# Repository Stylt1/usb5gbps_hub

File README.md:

View this project on [CADLAB.io](https://cadlab.io/project/30484). 

# usb5gbps_hub
USB-C hub that works on USB 3.2 Gen 1 protocol

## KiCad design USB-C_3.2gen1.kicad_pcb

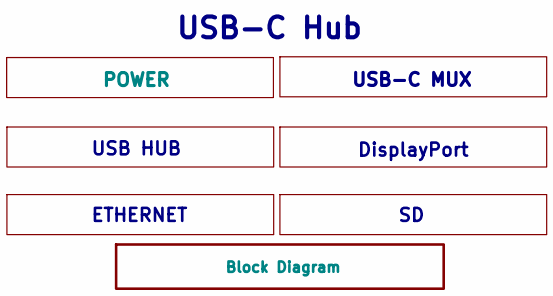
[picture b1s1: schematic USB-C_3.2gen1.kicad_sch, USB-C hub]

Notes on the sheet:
DisplayPort
USB-C MUX
USB HUB
ETHERNET
USB-C Hub

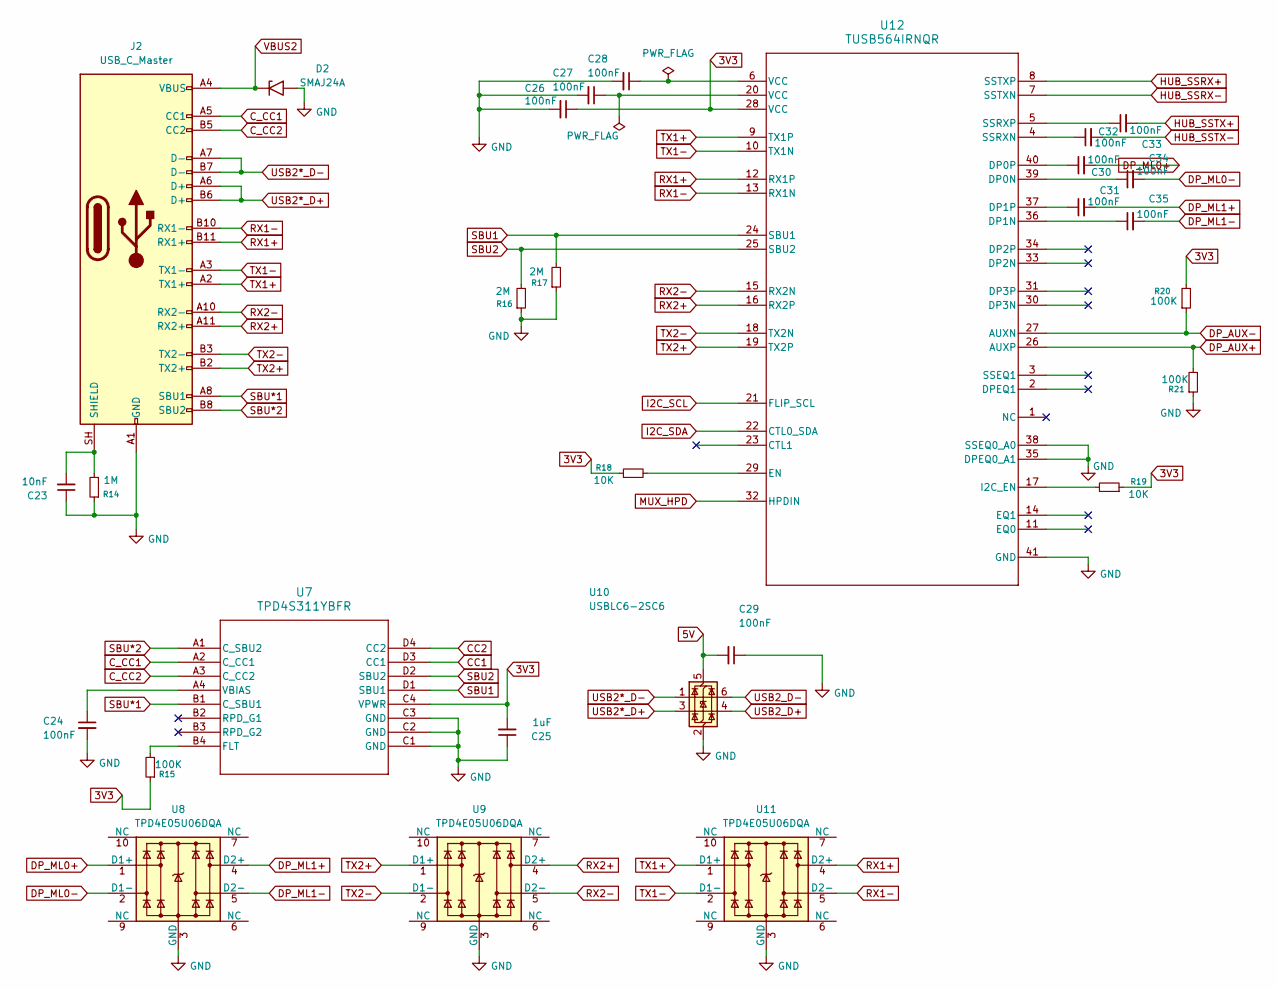
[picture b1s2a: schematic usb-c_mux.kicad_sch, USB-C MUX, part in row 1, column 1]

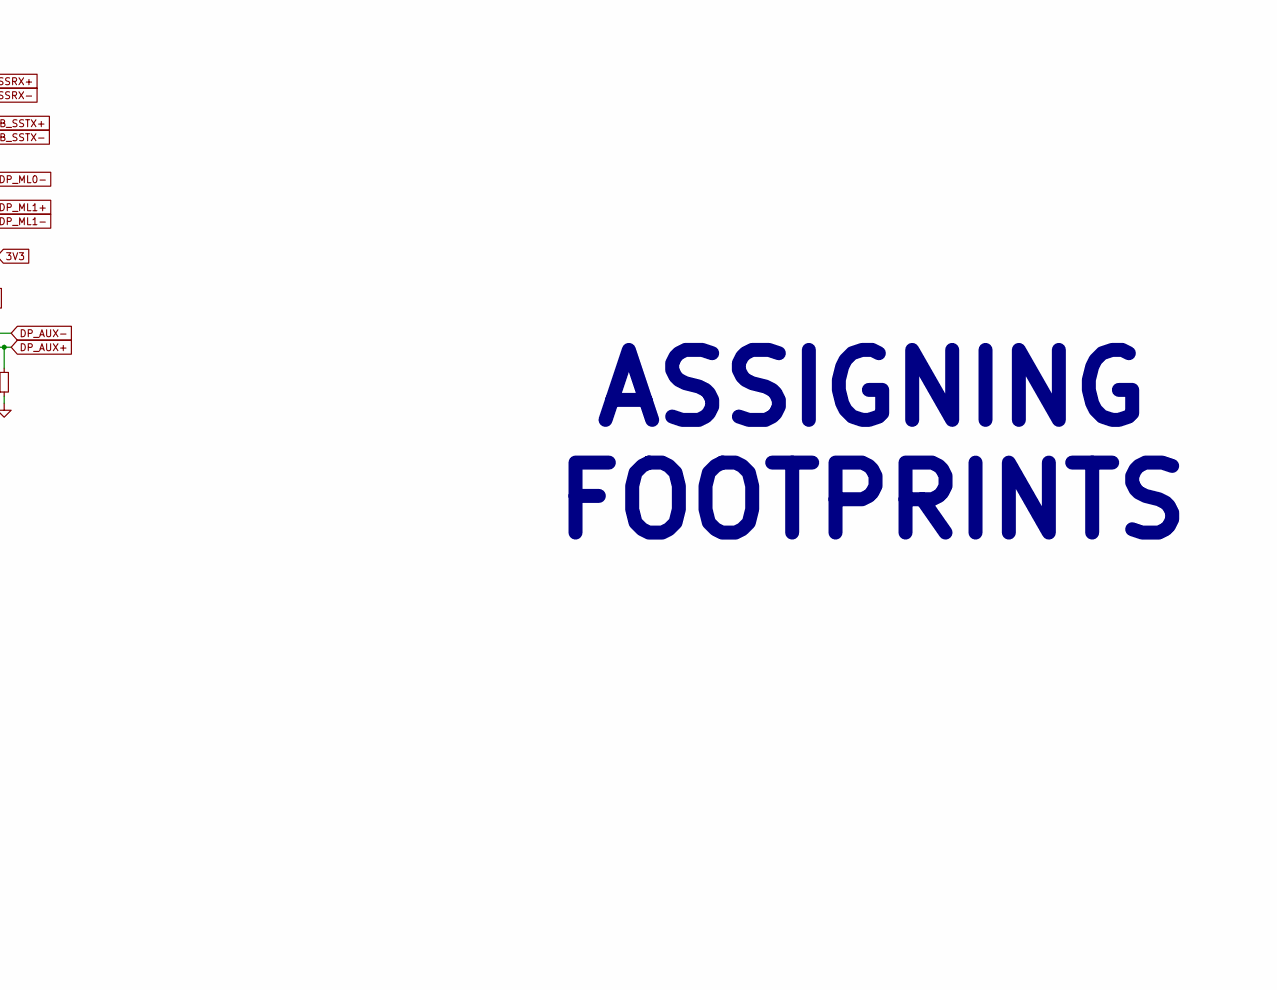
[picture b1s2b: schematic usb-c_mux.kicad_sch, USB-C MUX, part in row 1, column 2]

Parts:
C23: 10nF; C_0603_1608Metric
C24, C26, C27, C28, C29, C30, C31, C32, C33, C34, C35: 100nF; C_0603_1608Metric
C25: 1uF; C_0603_1608Metric
D2: SMAJ24A; D_SMA
J2: USB_C_Master; USB_C_Receptacle_Molex_105450-0101
R14: 1M; R_0603_1608Metric
R15, R20, R21: 100K; R_0603_1608Metric
R16, R17: 2M; R_0603_1608Metric
R18, R19: 10K; R_0603_1608Metric
U7: TPD4S311YBFR; Texas_DSBGA-16_2.39x2.39mm_Layout4x4_P0.5mm
U8, U9, U11: TPD4E05U06DQA; USON-10_2.5x1.0mm_P0.5mm
U10: USBLC6-2SC6; SOT-23-6
U12: TUSB564IRNQR; Texas_RNQ0040A_WQFN-40-1EP_6x4mm_P0.4mm_EP4.7x2.7mm_Thermal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

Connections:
3V3: C25.2, C26.1, R15.1, R18.1, R19.1, R20.2, U7.C4 (VPWR), U12.28 (VCC); also elsewhere on the board
5V: C29.2, U10.5 (VBUS); also elsewhere on the board
CC1: U7.D3 (CC1)
CC2: U7.D4 (CC2)
C_CC1: J2.A5 (CC1), U7.A2 (C_CC1)
C_CC2: J2.B5 (CC2), U7.A3 (C_CC2)
DP_AUX+: R21.2, U12.26 (AUXP); also elsewhere on the board
DP_AUX-: R20.1, U12.27 (AUXN); also elsewhere on the board
DP_ML0+: C30.2, U8.1 (D1+); also elsewhere on the board
DP_ML0-: C34.2, U8.2 (D1-); also elsewhere on the board
DP_ML1+: C31.2, U8.4 (D2+); also elsewhere on the board
DP_ML1-: C35.2, U8.5 (D2-); also elsewhere on the board
GND: C23.1, C24.2, C25.1, C26.2, C27.2, C28.2, C29.1, D2.2 (A2), J2.A1 (GND), J2.A12 (GND), J2.B1 (GND), J2.B12 (GND), R14.1, R16.1, R17.1, R21.1, U7.C1 (GND), U7.C2 (GND), U7.C3 (GND), U8.3 (GND), U8.8 (GND), U9.3 (GND), U9.8 (GND), U10.2 (GND), U11.3 (GND), U11.8 (GND), U12.35 (DPEQ0_A1), U12.38 (SSEQ0_A0), U12.41 (GND); also elsewhere on the board
HUB_SSRX+: U12.8 (SSTXP); also elsewhere on the board
HUB_SSRX-: U12.7 (SSTXN); also elsewhere on the board
HUB_SSTX+: C33.2; also elsewhere on the board
HUB_SSTX-: C32.2; also elsewhere on the board
I2C_SCL: U12.21 (FLIP_SCL); also elsewhere on the board
I2C_SDA: U12.22 (CTL0_SDA); also elsewhere on the board
MUX_HPD: U12.32 (HPDIN); also elsewhere on the board
unnamed: C27.1, U12.20 (VCC)
unnamed: C28.1, U12.6 (VCC)
unnamed: C23.2, J2.SH (SHIELD), R14.2
unnamed: R15.2, U7.B4 (FLT)
unnamed: C24.1, U7.A4 (VBIAS)
unnamed: C34.1, U12.39 (DP0N)
unnamed: C30.1, U12.40 (DP0P)
unnamed: C35.1, U12.36 (DP1N)
unnamed: C31.1, U12.37 (DP1P)
unnamed: R18.2, U12.29 (EN)
unnamed: R19.2, U12.17 (I2C_EN)
unnamed: C32.1, U12.4 (SSRXN)
unnamed: C33.1, U12.5 (SSRXP)
RX1+: J2.B11 (RX1+), U11.4 (D2+), U12.12 (RX1P)
RX1-: J2.B10 (RX1-), U11.5 (D2-), U12.13 (RX1N)
RX2+: J2.A11 (RX2+), U9.4 (D2+), U12.16 (RX2P)
RX2-: J2.A10 (RX2-), U9.5 (D2-), U12.15 (RX2N)
SBU1: R17.2, U7.D1 (SBU1), U12.24 (SBU1)
SBU2: R16.2, U7.D2 (SBU2), U12.25 (SBU2)
SBU*1: J2.A8 (SBU1), U7.B1 (C_SBU1)
SBU*2: J2.B8 (SBU2), U7.A1 (C_SBU2)
TX1+: J2.A2 (TX1+), U11.1 (D1+), U12.9 (TX1P)
TX1-: J2.A3 (TX1-), U11.2 (D1-), U12.10 (TX1N)
TX2+: J2.B2 (TX2+), U9.1 (D1+), U12.19 (TX2P)
TX2-: J2.B3 (TX2-), U9.2 (D1-), U12.18 (TX2N)
USB2*_D+: J2.A6 (D+), J2.B6 (D+), U10.3 (I/O2)
USB2*_D-: J2.A7 (D-), J2.B7 (D-), U10.1 (I/O1)
USB2_D+: U10.4 (I/O2); also elsewhere on the board
USB2_D-: U10.6 (I/O1); also elsewhere on the board
VBUS2: D2.1 (A1), J2.A4 (VBUS), J2.A9 (VBUS), J2.B4 (VBUS), J2.B9 (VBUS); also elsewhere on the board

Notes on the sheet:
ASSIGNING FOOTPRINTS

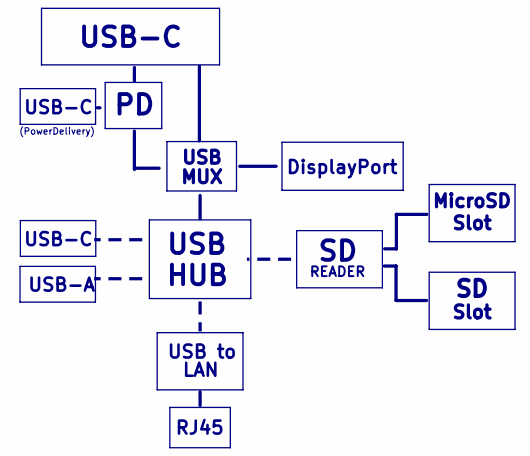
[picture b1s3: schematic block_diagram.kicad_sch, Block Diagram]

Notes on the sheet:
USB-C
HUB
LAN
USB-A
Slot
USB to
DisplayPort
USB
MicroSD
READER
USB-C
RJ45
MUX
(PowerDelivery)

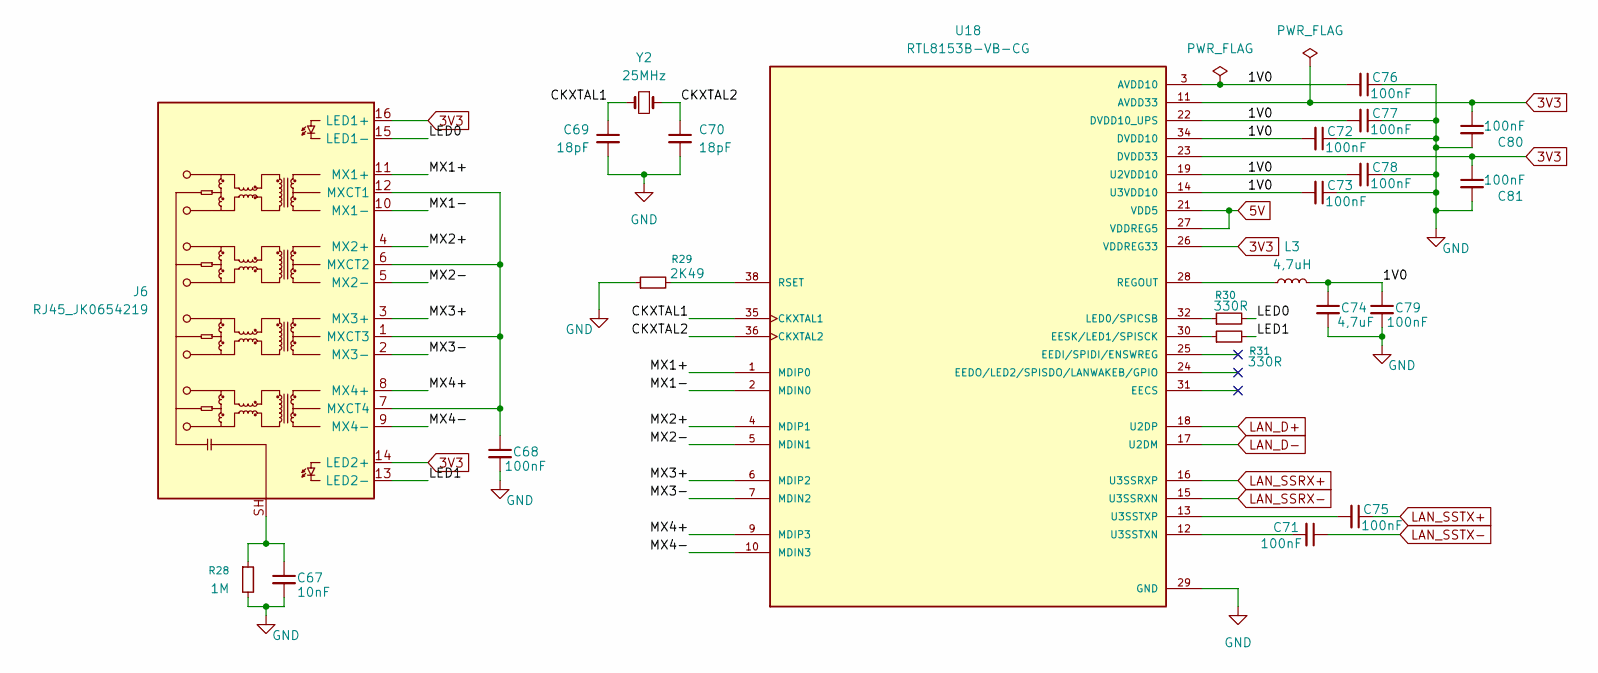
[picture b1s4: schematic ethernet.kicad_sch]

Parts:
C67: 10nF; C_0603_1608Metric
C68, C71, C72, C73, C75, C76, C77, C78, C79, C80, C81: 100nF; C_0603_1608Metric
C69, C70: 18pF; C_0603_1608Metric
C74: 4,7uF; C_1206_3216Metric
J6: RJ45_JK0654219; RJ45_Pulse_JK0654219NL_Horizontal
L3: 4,7uH; R_0603_1608Metric
R28: 1M; R_0603_1608Metric
R29: 2K49; R_0603_1608Metric
R30, R31: 330R; R_0603_1608Metric
U18: RTL8153B-VB-CG; QFN40P500X500X90-41N; PARTREV 1.4
Y2: 25MHz; Crystal_SMD_3225-4Pin_3.2x2.5mm

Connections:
3V3: C80.1, C81.1, J6.14 (LED2+), J6.16 (LED1+), U18.11 (AVDD33), U18.20 (AVDD33), U18.23 (DVDD33), U18.26 (VDDREG33), U18.33 (DVDD33), U18.39 (AVDD33), U18.40 (AVDD33); also elsewhere on the board
5V: U18.21 (VDD5), U18.27 (VDDREG5); also elsewhere on the board
/ETHERNET/CKXTAL1: C69.1, U18.35 (CKXTAL1), Y2.2
/ETHERNET/CKXTAL2: C70.1, U18.36 (CKXTAL2), Y2.1
/ETHERNET/LED0: J6.15 (LED1-), R30.2
/ETHERNET/LED1: J6.13 (LED2-), R31.2
/ETHERNET/MX1+: J6.11 (MX1+), U18.1 (MDIP0)
/ETHERNET/MX1-: J6.10 (MX1-), U18.2 (MDIN0)
/ETHERNET/MX2+: J6.4 (MX2+), U18.4 (MDIP1)
/ETHERNET/MX2-: J6.5 (MX2-), U18.5 (MDIN1)
/ETHERNET/MX3+: J6.3 (MX3+), U18.6 (MDIP2)
/ETHERNET/MX3-: J6.2 (MX3-), U18.7 (MDIN2)
/ETHERNET/MX4+: J6.8 (MX4+), U18.9 (MDIP3)
/ETHERNET/MX4-: J6.9 (MX4-), U18.10 (MDIN3)
AVDD10: C72.2, C73.2, C74.1, C76.2, C77.2, C78.2, C79.1, L3.2, U18.3 (AVDD10), U18.8 (AVDD10), U18.14 (U3VDD10), U18.19 (U2VDD10), U18.22 (DVDD10_UPS), U18.34 (DVDD10), U18.37 (AVDD10)
GND: C67.2, C68.2, C69.2, C70.2, C72.1, C73.1, C74.2, C76.1, C77.1, C78.1, C79.2, C80.2, C81.2, R28.2, R29.1, U18.29 (GND), U18.41 (GND); also elsewhere on the board
LAN_D+: U18.18 (U2DP); also elsewhere on the board
LAN_D-: U18.17 (U2DM); also elsewhere on the board
LAN_SSRX+: U18.16 (U3SSRXP); also elsewhere on the board
LAN_SSRX-: U18.15 (U3SSRXN); also elsewhere on the board
LAN_SSTX+: C75.1; also elsewhere on the board
LAN_SSTX-: C71.1; also elsewhere on the board
unnamed: C67.1, J6.SH, R28.1
unnamed: C68.1, J6.1 (MXCT3), J6.6 (MXCT2), J6.7 (MXCT4), J6.12 (MXCT1)
unnamed: R31.1, U18.30 (EESK/LED1/SPISCK)
unnamed: R30.1, U18.32 (LED0/SPICSB)
unnamed: L3.1, U18.28 (REGOUT)
unnamed: R29.2, U18.38 (RSET)
unnamed: C71.2, U18.12 (U3SSTXN)
unnamed: C75.2, U18.13 (U3SSTXP)

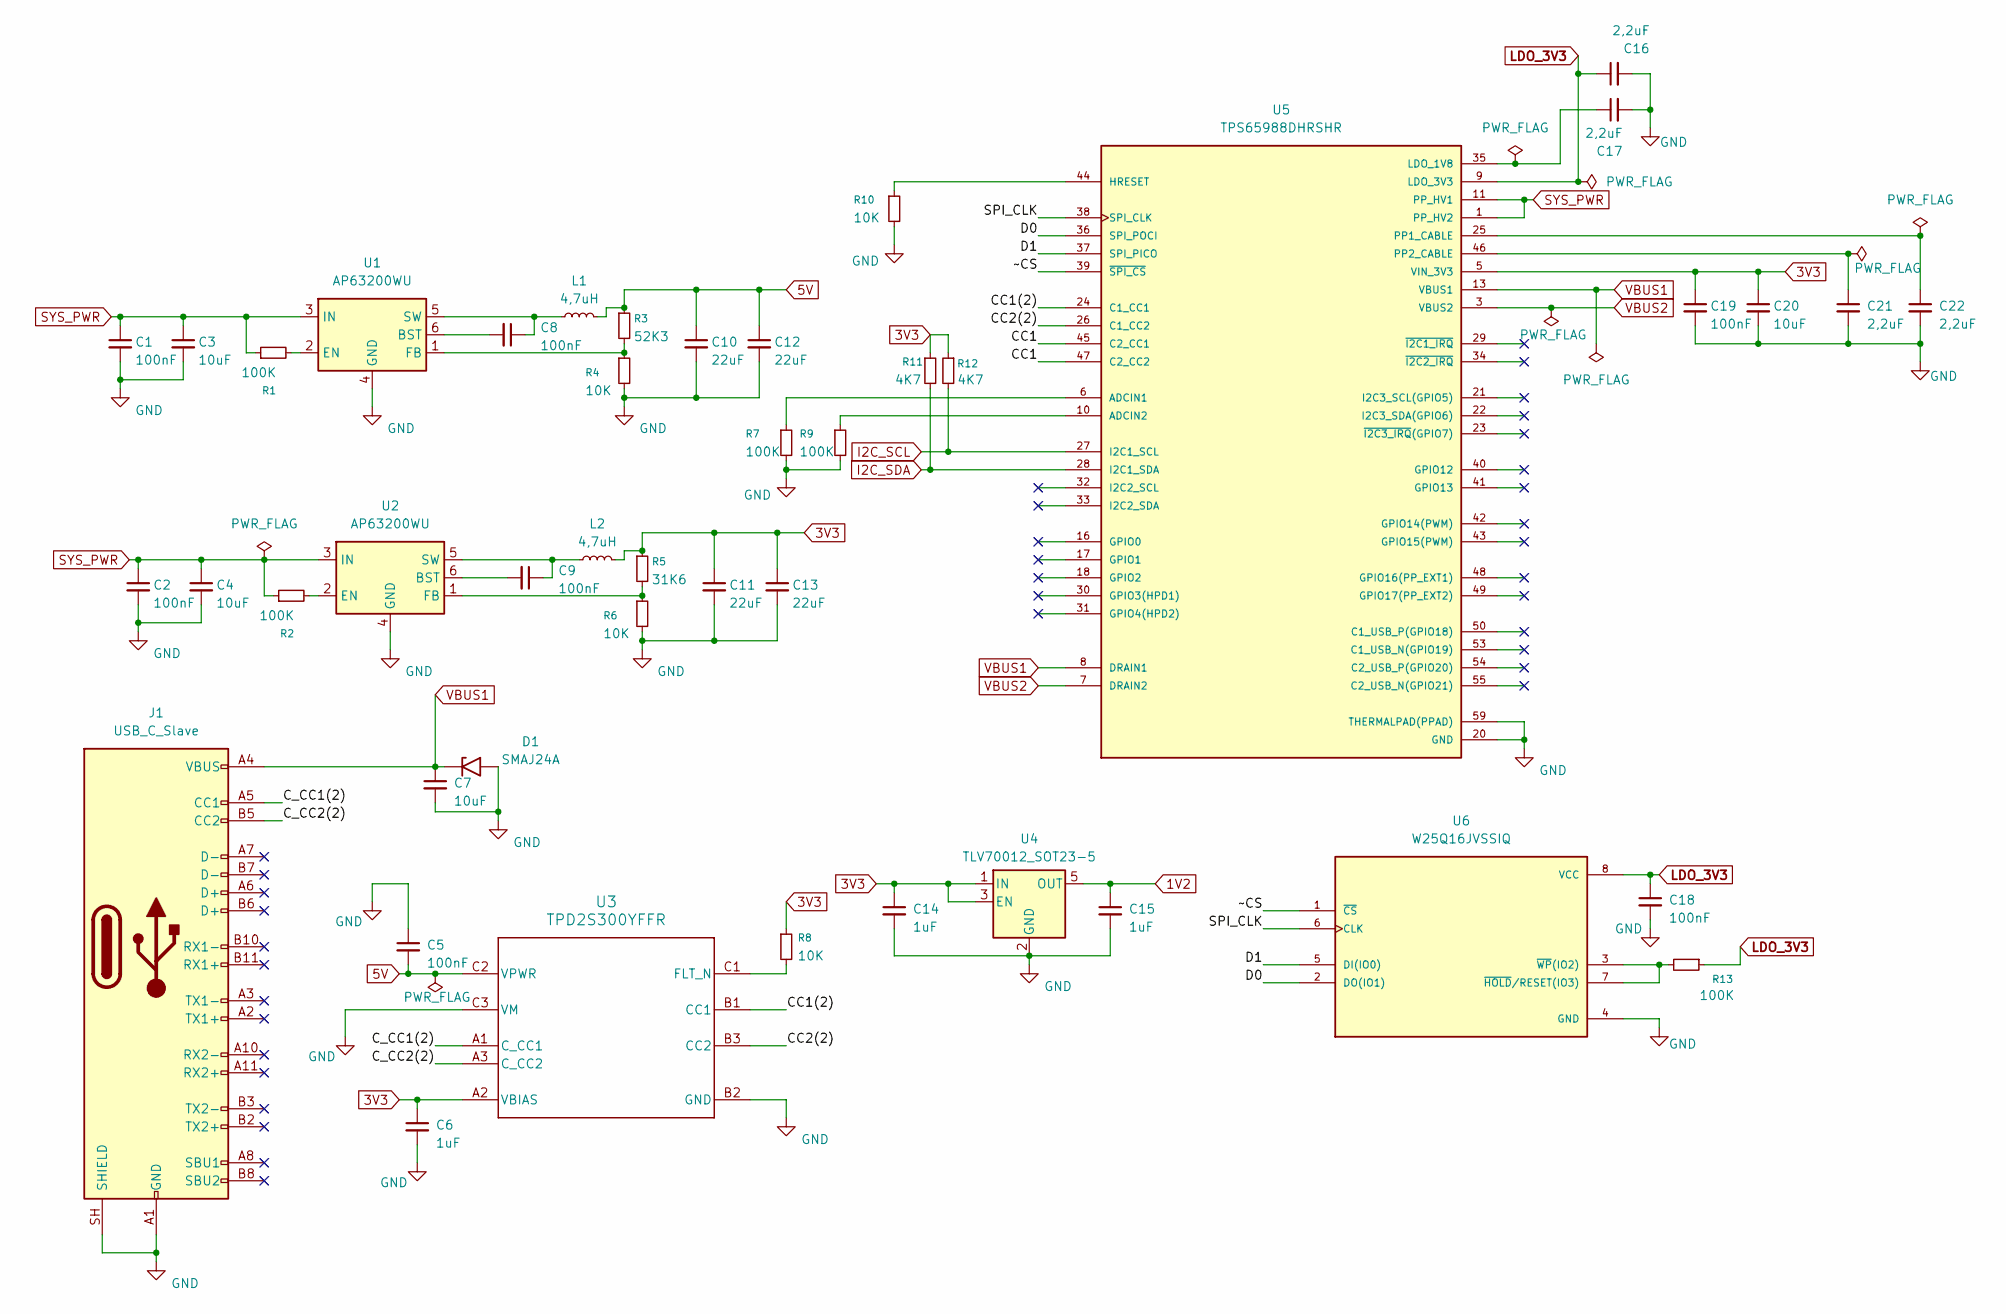
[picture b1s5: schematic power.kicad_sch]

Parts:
C1, C2, C5, C8, C9, C18, C19: 100nF; C_0603_1608Metric
C3, C4, C7, C20: 10uF; C_1206_3216Metric
C6, C14, C15: 1uF; C_0603_1608Metric
C10, C11, C12, C13: 22uF; C_1206_3216Metric
C16, C17, C21, C22: 2,2uF; C_0603_1608Metric
D1: SMAJ24A; D_SMA
J1: USB_C_Slave; USB_C_Receptacle_Molex_105450-0101
L1, L2: 4,7uH; L_6.3x6.3_H3
R1, R2, R7, R9, R13: 100K; R_0603_1608Metric
R3: 52K3; R_0603_1608Metric
R4, R6, R8, R10: 10K; R_0603_1608Metric
R5: 31K6; R_0603_1608Metric
R11, R12: 4K7; R_0603_1608Metric
U1, U2: AP63200WU; TSOT-23-6
U3: TPD2S300YFFR; Texas_DSBGA-9_1.4715x1.4715mm_Layout3x3_P0.5mm
U4: TLV70012_SOT23-5; SOT-23-5
U5: TPS65988DHRSHR; IC_TPS65987DDHRSHR; PARTREV AUGUST 2021
U6: W25Q16JVSSIQ; SOIC127P790X216-8N

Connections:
1V2: C15.1, U4.5 (OUT); also elsewhere on the board
3V3: C6.1, C11.1, C13.1, C14.1, C19.1, C20.1, L2.2, R5.1, R8.1, R11.1, R12.1, U3.A2 (VBIAS), U4.1 (IN), U4.3 (EN), U5.5 (VIN_3V3); also elsewhere on the board
5V: C5.2, C10.1, C12.1, L1.2, R3.1, U3.C2 (VPWR); also elsewhere on the board
/POWER/CC1: U5.45 (C2_CC1), U5.47 (C2_CC2)
/POWER/CC1(2): U3.B1 (CC1), U5.24 (C1_CC1)
/POWER/CC2(2): U3.B3 (CC2), U5.26 (C1_CC2)
/POWER/C_CC1(2): J1.A5 (CC1), U3.A1 (C_CC1)
/POWER/C_CC2(2): J1.B5 (CC2), U3.A3 (C_CC2)
/POWER/D0: U5.36 (SPI_POCI), U6.2 (DO(IO1))
/POWER/D1: U5.37 (SPI_PICO), U6.5 (DI(IO0))
/POWER/SPI_CLK: U5.38 (SPI_CLK), U6.6 (CLK)
/POWER/~CS: U5.39 (~SPI_CS), U6.1 (~CS)
GND: C1.2, C2.2, C3.2, C4.2, C5.1, C6.2, C7.2, C10.2, C11.2, C12.2, C13.2, C14.2, C15.2, C16.2, C17.2, C18.2, C19.2, C20.2, C21.2, C22.2, D1.2 (A2), J1.A1 (GND), J1.A12 (GND), J1.B1 (GND), J1.B12 (GND), J1.SH (SHIELD), R4.2, R6.2, R7.2, R9.2, R10.2, U1.4 (GND), U2.4 (GND), U3.B2 (GND), U3.C3 (VM), U4.2 (GND), U5.20 (GND), U5.51 (GND), U5.59 (THERMALPAD(PPAD)), U6.4 (GND); also elsewhere on the board
I2C_SCL: R12.2, U5.27 (I2C1_SCL); also elsewhere on the board
I2C_SDA: R11.2, U5.28 (I2C1_SDA); also elsewhere on the board
LDO_3V3: C16.1, C18.1, R13.1, U5.9 (LDO_3V3), U6.8 (VCC)
unnamed: C8.2, U1.6 (BST)
unnamed: R1.2, U1.2 (EN)
unnamed: R3.2, R4.1, U1.1 (FB)
unnamed: C8.1, L1.1, U1.5 (SW)
unnamed: C9.2, U2.6 (BST)
unnamed: R2.2, U2.2 (EN)
unnamed: R5.2, R6.1, U2.1 (FB)
unnamed: C9.1, L2.1, U2.5 (SW)
unnamed: R8.2, U3.C1 (FLT_N)
unnamed: R7.1, U5.6 (ADCIN1)
unnamed: R9.1, U5.10 (ADCIN2)
unnamed: R10.1, U5.44 (HRESET)
unnamed: C17.1, U5.35 (LDO_1V8)
unnamed: C22.1, U5.25 (PP1_CABLE)
unnamed: C21.1, U5.46 (PP2_CABLE)
unnamed: R13.2, U6.3 (~WP(IO2)), U6.7 (~HOLD/RESET(IO3))
SYS_PWR: C1.1, C2.1, C3.1, C4.1, R1.1, R2.1, U1.3 (IN), U2.3 (IN), U5.1 (PP_HV2), U5.11 (PP_HV1)
VBUS1: C7.1, D1.1 (A1), J1.A4 (VBUS), J1.A9 (VBUS), J1.B4 (VBUS), J1.B9 (VBUS), U5.8 (DRAIN1), U5.13 (VBUS1), U5.15 (DRAIN1), U5.19 (DRAIN1), U5.58 (DRAIN1)
VBUS2: U5.3 (VBUS2), U5.7 (DRAIN2), U5.52 (DRAIN2), U5.56 (DRAIN2), U5.57 (DRAIN2); also elsewhere on the board

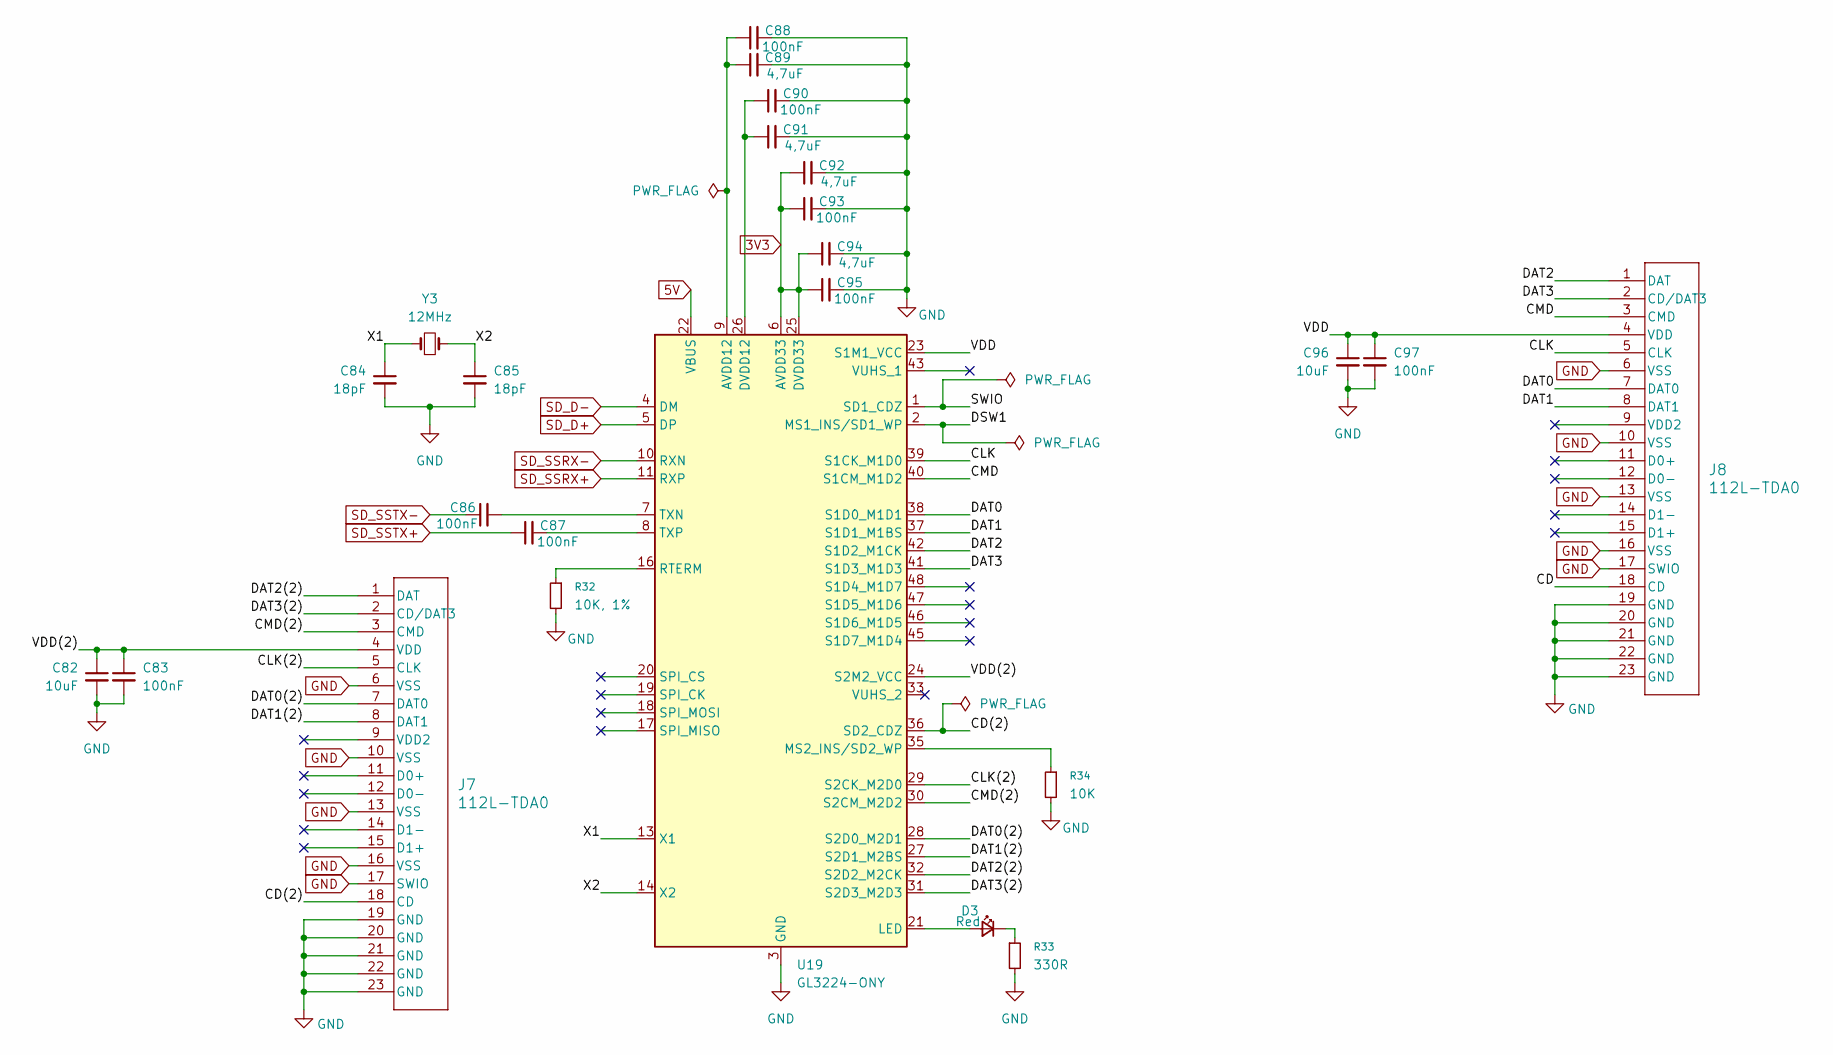
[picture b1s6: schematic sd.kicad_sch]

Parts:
C82, C96: 10uF; C_1206_3216Metric
C83, C86, C87, C88, C90, C93, C95, C97: 100nF; C_0603_1608Metric
C84, C85: 18pF; C_0603_1608Metric
C89, C91, C92, C94: 4,7uF; C_1206_3216Metric
D3: Red; LED_0603_1608Metric
J7, J8: 112L-TDA0; CONN_112L-TDA0_ATT
R32: 10K, 1%; R_0603_1608Metric
R33: 330R; R_0603_1608Metric
R34: 10K; R_0603_1608Metric
U19: GL3224-ONY; QFN-48-1EP_7x7mm_P0.5mm_EP5.15x5.15mm
Y3: 12MHz; Crystal_SMD_3225-4Pin_3.2x2.5mm

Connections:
3V3: C92.1, C93.1, C94.1, C95.1, U19.6 (AVDD33), U19.15 (AVDD33), U19.25 (DVDD33), U19.34 (DVDD33), U19.44 (DVDD33); also elsewhere on the board
5V: U19.22 (VBUS); also elsewhere on the board
/SD/CD: J8.18 (CD)
/SD/CD(2): J7.18 (CD), U19.36 (SD2_CDZ)
/SD/CLK: J8.5 (CLK), U19.39 (S1CK_M1D0)
/SD/CLK(2): J7.5 (CLK), U19.29 (S2CK_M2D0)
/SD/CMD: J8.3 (CMD), U19.40 (S1CM_M1D2)
/SD/CMD(2): J7.3 (CMD), U19.30 (S2CM_M2D2)
/SD/DAT0: J8.7 (DAT0), U19.38 (S1D0_M1D1)
/SD/DAT0(2): J7.7 (DAT0), U19.28 (S2D0_M2D1)
/SD/DAT1: J8.8 (DAT1), U19.37 (S1D1_M1BS)
/SD/DAT1(2): J7.8 (DAT1), U19.27 (S2D1_M2BS)
/SD/DAT2: J8.1 (DAT), U19.42 (S1D2_M1CK)
/SD/DAT2(2): J7.1 (DAT), U19.32 (S2D2_M2CK)
/SD/DAT3: J8.2 (CD/DAT3), U19.41 (S1D3_M1D3)
/SD/DAT3(2): J7.2 (CD/DAT3), U19.31 (S2D3_M2D3)
/SD/DSW1: U19.2 (MS1_INS/SD1_WP)
/SD/SWIO: U19.1 (SD1_CDZ)
/SD/VDD: C96.1, C97.1, J8.4 (VDD), U19.23 (S1M1_VCC)
/SD/VDD(2): C82.1, C83.1, J7.4 (VDD), U19.24 (S2M2_VCC)
/SD/X1: C84.1, U19.13 (X1), Y3.1
/SD/X2: C85.1, U19.14 (X2), Y3.2
GND: C82.2, C83.2, C84.2, C85.2, C88.2, C89.2, C90.2, C91.2, C92.2, C93.2, C94.2, C95.2, C96.2, C97.2, J7.6 (VSS), J7.10 (VSS), J7.13 (VSS), J7.16 (VSS), J7.17 (SWIO), J7.19 (GND), J7.20 (GND), J7.21 (GND), J7.22 (GND), J7.23 (GND), J8.6 (VSS), J8.10 (VSS), J8.13 (VSS), J8.16 (VSS), J8.17 (SWIO), J8.19 (GND), J8.20 (GND), J8.21 (GND), J8.22 (GND), J8.23 (GND), R32.2, R33.2, R34.2, U19.3 (GND), U19.12 (GND), U19.49 (GND); also elsewhere on the board
unnamed: D3.2 (A), U19.21 (LED)
unnamed: D3.1 (K), R33.1
unnamed: C88.1, C89.1, U19.9 (AVDD12)
unnamed: C90.1, C91.1, U19.26 (DVDD12)
unnamed: R34.1, U19.35 (MS2_INS/SD2_WP)
unnamed: R32.1, U19.16 (RTERM)
unnamed: C86.2, U19.7 (TXN)
unnamed: C87.2, U19.8 (TXP)
SD_D+: U19.5 (DP); also elsewhere on the board
SD_D-: U19.4 (DM); also elsewhere on the board
SD_SSRX+: U19.11 (RXP); also elsewhere on the board
SD_SSRX-: U19.10 (RXN); also elsewhere on the board
SD_SSTX+: C87.1; also elsewhere on the board
SD_SSTX-: C86.1; also elsewhere on the board

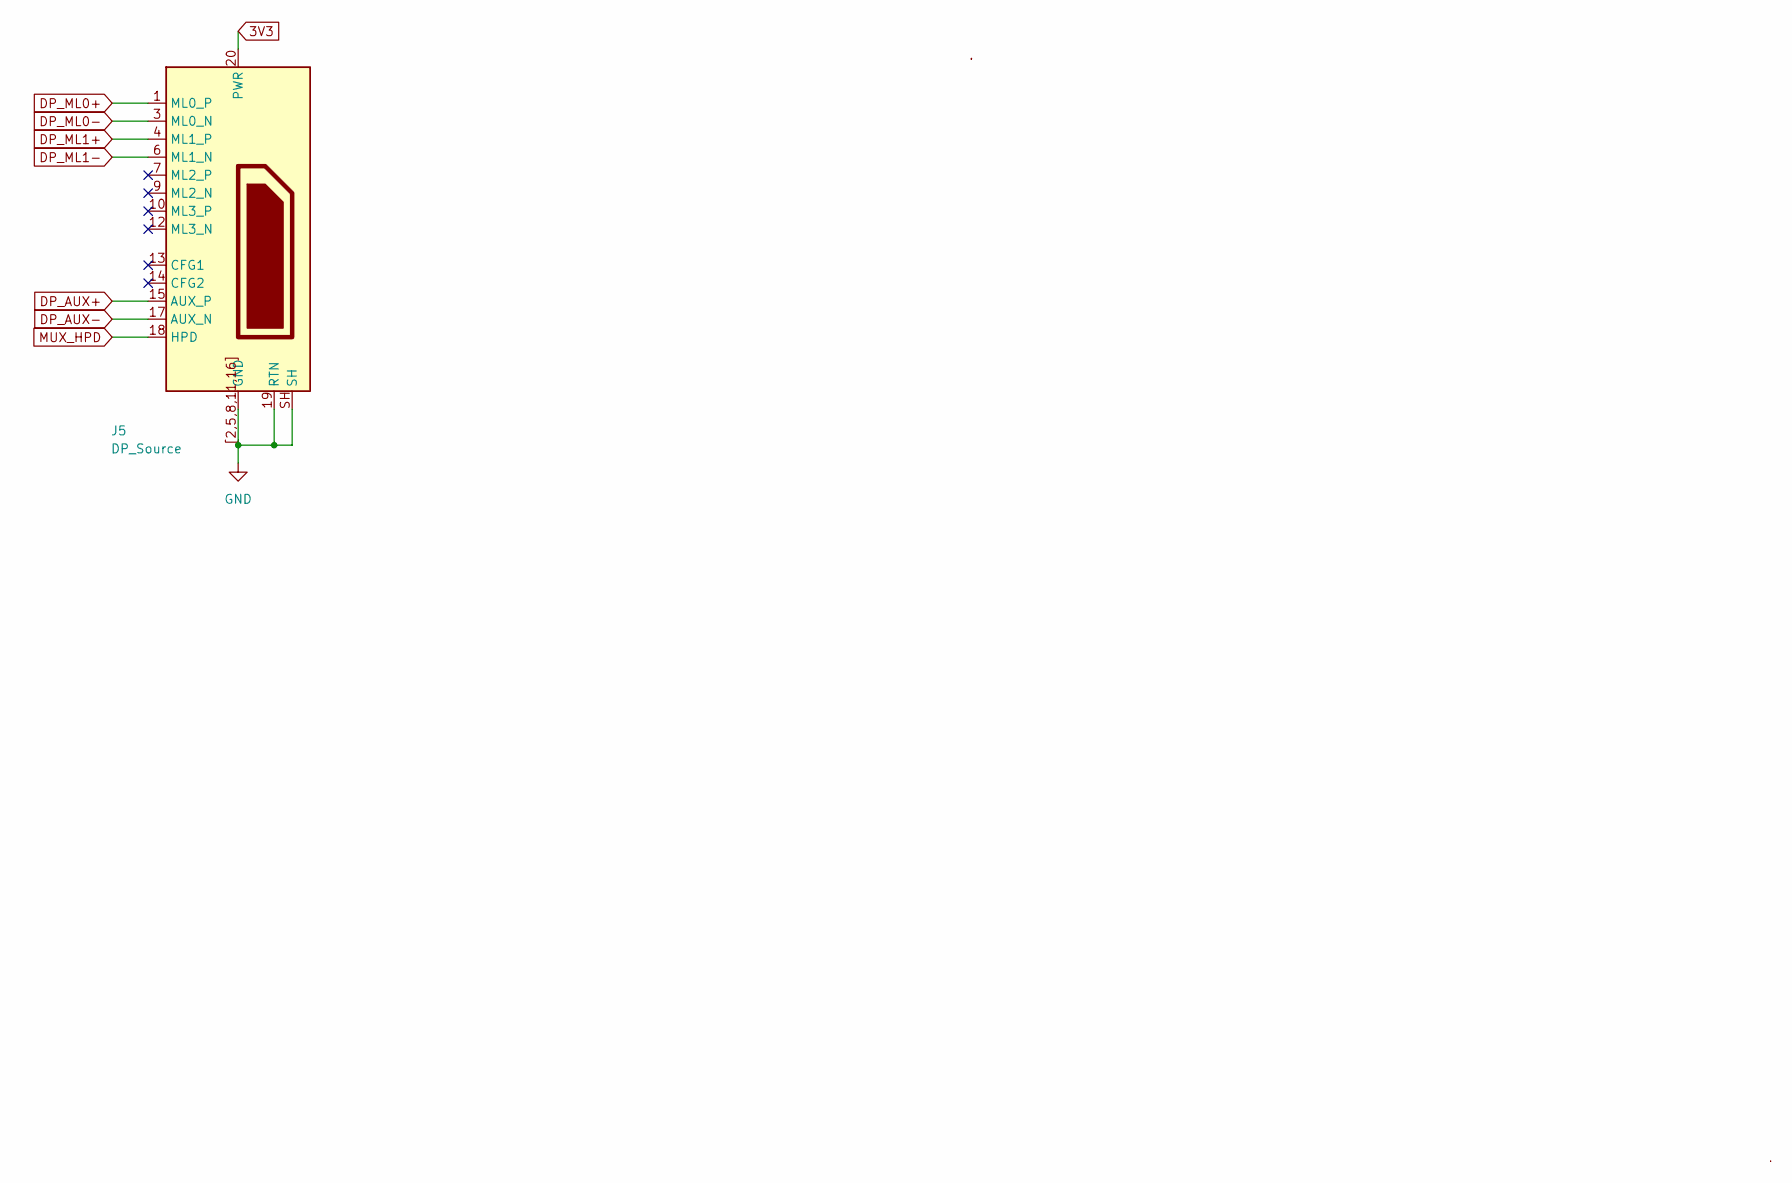
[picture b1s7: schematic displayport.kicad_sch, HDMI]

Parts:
J5: DP_Source; AMPHENOL_DPF20102741TR

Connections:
3V3: J5.20 (PWR); also elsewhere on the board
DP_AUX+: J5.15 (AUX_P); also elsewhere on the board
DP_AUX-: J5.17 (AUX_N); also elsewhere on the board
DP_ML0+: J5.1 (ML0_P); also elsewhere on the board
DP_ML0-: J5.3 (ML0_N); also elsewhere on the board
DP_ML1+: J5.4 (ML1_P); also elsewhere on the board
DP_ML1-: J5.6 (ML1_N); also elsewhere on the board
GND: J5.2 (GND), J5.5 (GND), J5.8 (GND), J5.11 (GND), J5.16 (GND), J5.19 (RTN), J5.SH, J5.[2,5,8,11,16] (GND); also elsewhere on the board
MUX_HPD: J5.18 (HPD); also elsewhere on the board

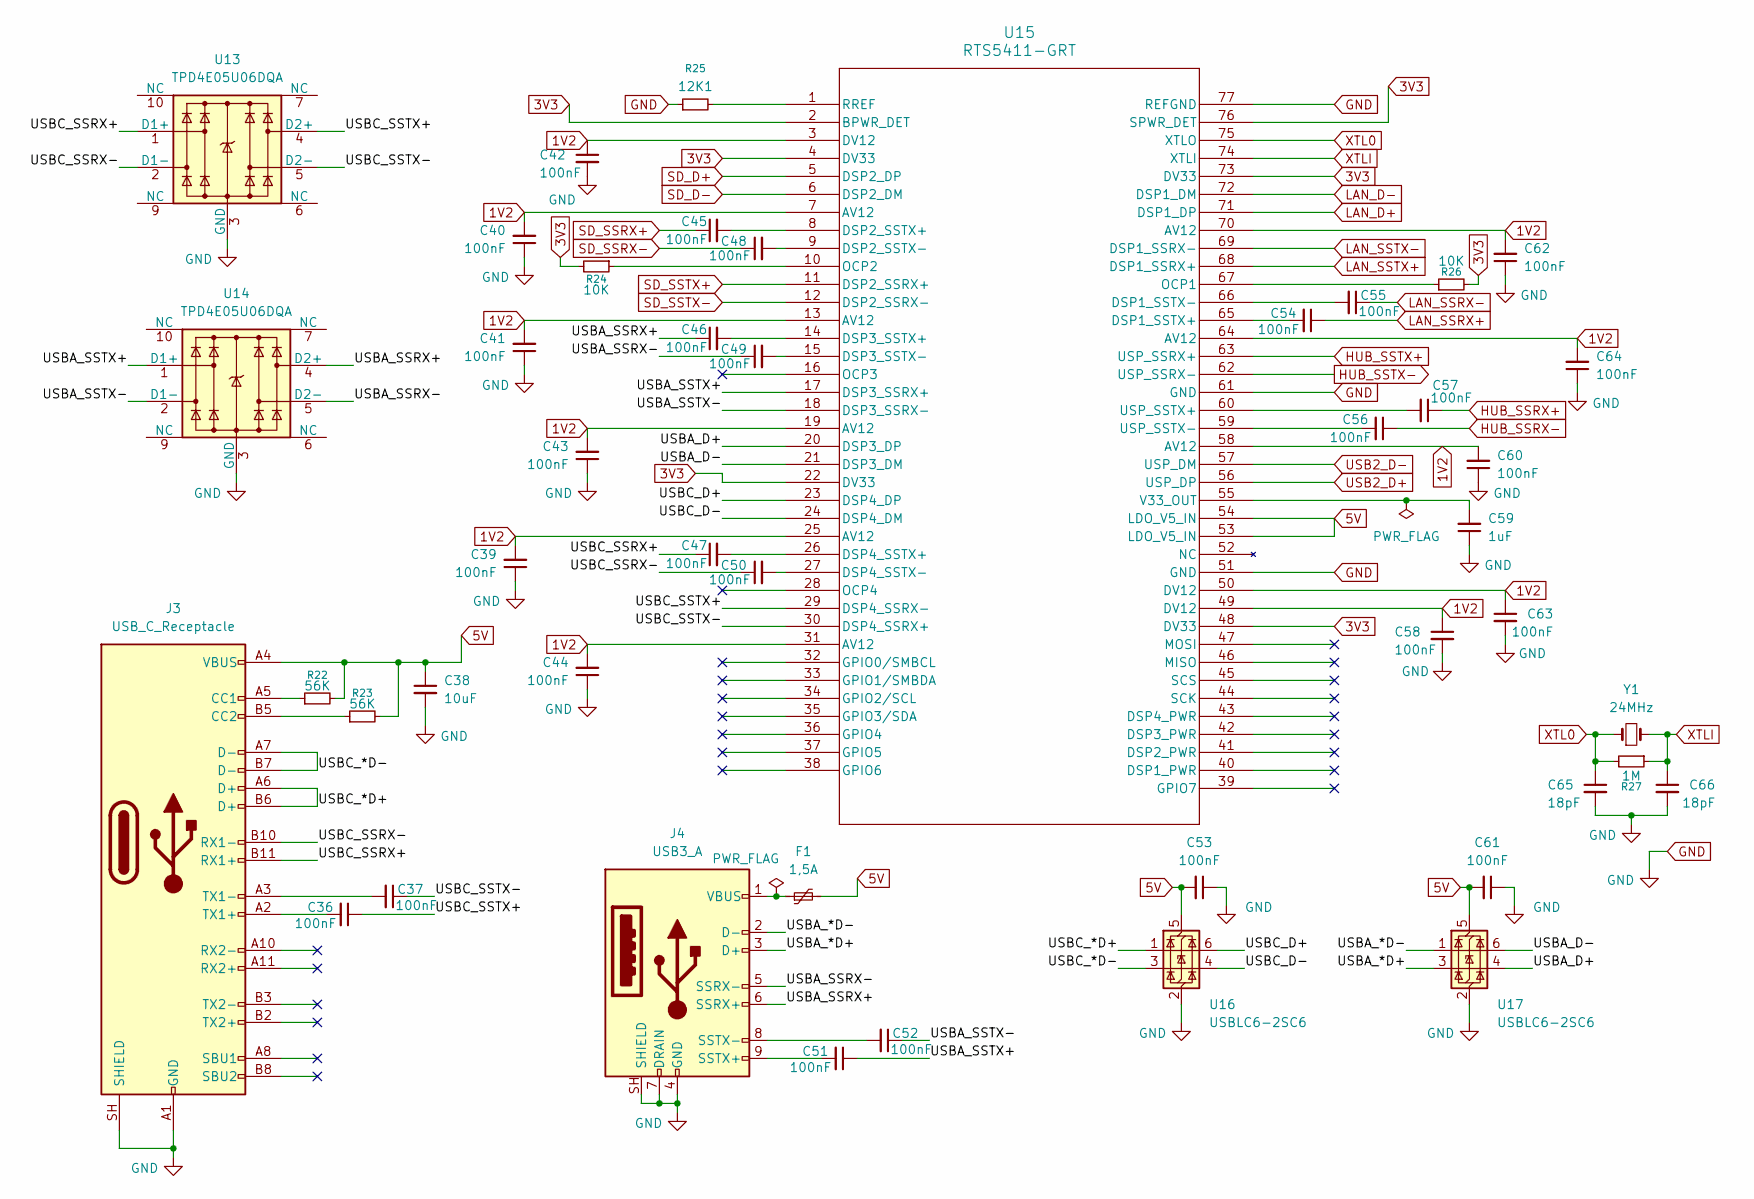
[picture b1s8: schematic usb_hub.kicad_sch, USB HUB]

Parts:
C36, C37, C39, C40, C41, C42, C43, C44, C45, C46, C47, C48, C49, C50, C51, C52, C53, C54, C55, C56, C57, C58, C60, C61, C62, C63, C64: 100nF; C_0603_1608Metric
C38: 10uF; C_1206_3216Metric
C59: 1uF; C_0603_1608Metric
C65, C66: 18pF; C_0603_1608Metric
F1: 1,5A; Fuse_1206_3216Metric
J3: USB_C_Receptacle; USB_C_Receptacle_Molex_105450-0101
J4: USB3_A; USB3_A_Plug_Wuerth_692112030100_Horizontal
R22, R23: 56K; R_0603_1608Metric
R24, R26: 10K; R_0603_1608Metric
R25: 12K1; R_0603_1608Metric
R27: 1M; R_0603_1608Metric
U13, U14: TPD4E05U06DQA; USON-10_2.5x1.0mm_P0.5mm
U15: RTS5411-GRT; QFN-76-1EP_9x9mm_P0.4mm_EP5.81x6.31mm_ThermalVias
U16, U17: USBLC6-2SC6; SOT-23-6
Y1: 24MHz; Crystal_SMD_3225-4Pin_3.2x2.5mm

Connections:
1V2: C39.2, C40.2, C41.2, C42.1, C43.2, C44.2, C58.1, C60.2, C62.2, C63.1, C64.2, U15.3 (DV12), U15.7 (AV12), U15.13 (AV12), U15.19 (AV12), U15.25 (AV12), U15.31 (AV12), U15.49 (DV12), U15.50 (DV12), U15.58 (AV12), U15.64 (AV12), U15.70 (AV12); also elsewhere on the board
3V3: R24.2, R26.2, U15.2 (BPWR_DET), U15.4 (DV33), U15.22 (DV33), U15.48 (DV33), U15.73 (DV33), U15.76 (SPWR_DET); also elsewhere on the board
5V: C38.1, C53.2, C61.2, F1.2, J3.A4 (VBUS), J3.A9 (VBUS), J3.B4 (VBUS), J3.B9 (VBUS), R22.2, R23.2, U15.53 (LDO_V5_IN), U15.54 (LDO_V5_IN), U16.5 (VBUS), U17.5 (VBUS); also elsewhere on the board
/USB HUB/USBA_*D+: J4.3 (D+), U17.3 (I/O2)
/USB HUB/USBA_*D-: J4.2 (D-), U17.1 (I/O1)
/USB HUB/USBA_D+: U15.20 (DSP3_DP), U17.4 (I/O2)
/USB HUB/USBA_D-: U15.21 (DSP3_DM), U17.6 (I/O1)
/USB HUB/USBA_SSRX+: C46.1, J4.6 (SSRX+), U14.4 (D2+)
/USB HUB/USBA_SSRX-: C49.1, J4.5 (SSRX-), U14.5 (D2-)
/USB HUB/USBA_SSTX+: C51.1, U14.1 (D1+), U15.17 (DSP3_SSRX+)
/USB HUB/USBA_SSTX-: C52.1, U14.2 (D1-), U15.18 (DSP3_SSRX-)
/USB HUB/USBC_*D+: J3.A6 (D+), J3.B6 (D+), U16.1 (I/O1)
/USB HUB/USBC_*D-: J3.A7 (D-), J3.B7 (D-), U16.3 (I/O2)
/USB HUB/USBC_D+: U15.23 (DSP4_DP), U16.6 (I/O1)
/USB HUB/USBC_D-: U15.24 (DSP4_DM), U16.4 (I/O2)
/USB HUB/USBC_SSRX+: C47.1, J3.B11 (RX1+), U13.1 (D1+)
/USB HUB/USBC_SSRX-: C50.1, J3.B10 (RX1-), U13.2 (D1-)
/USB HUB/USBC_SSTX+: C36.1, U13.4 (D2+), U15.29 (DSP4_SSRX-)
/USB HUB/USBC_SSTX-: C37.1, U13.5 (D2-), U15.30 (DSP4_SSRX+)
GND: C38.2, C39.1, C40.1, C41.1, C42.2, C43.1, C44.1, C53.1, C58.2, C59.1, C60.1, C61.1, C62.1, C63.2, C64.1, C65.2, C66.2, J3.A1 (GND), J3.A12 (GND), J3.B1 (GND), J3.B12 (GND), J3.SH (SHIELD), J4.4 (GND), J4.7 (DRAIN), J4.SH (SHIELD), R25.1, U13.3 (GND), U13.8 (GND), U14.3 (GND), U14.8 (GND), U15.51 (GND), U15.61 (GND), U15.77 (REFGND), U16.2 (GND), U17.2 (GND); also elsewhere on the board
HUB_SSRX+: C57.1; also elsewhere on the board
HUB_SSRX-: C56.1; also elsewhere on the board
HUB_SSTX+: U15.63 (USP_SSRX+); also elsewhere on the board
HUB_SSTX-: U15.62 (USP_SSRX-); also elsewhere on the board
LAN_D+: U15.71 (DSP1_DP); also elsewhere on the board
LAN_D-: U15.72 (DSP1_DM); also elsewhere on the board
LAN_SSRX+: C54.1; also elsewhere on the board
LAN_SSRX-: C55.1; also elsewhere on the board
LAN_SSTX+: U15.68 (DSP1_SSRX+); also elsewhere on the board
LAN_SSTX-: U15.69 (DSP1_SSRX-); also elsewhere on the board
unnamed: J3.A5 (CC1), R22.1
unnamed: J3.B5 (CC2), R23.1
unnamed: C36.2, J3.A2 (TX1+)
unnamed: C37.2, J3.A3 (TX1-)
unnamed: C51.2, J4.9 (SSTX+)
unnamed: C52.2, J4.8 (SSTX-)
unnamed: F1.1, J4.1 (VBUS)
unnamed: C54.2, U15.65 (DSP1_SSTX+)
unnamed: C55.2, U15.66 (DSP1_SSTX-)
unnamed: C45.2, U15.8 (DSP2_SSTX+)
unnamed: C48.2, U15.9 (DSP2_SSTX-)
unnamed: C46.2, U15.14 (DSP3_SSTX+)
unnamed: C49.2, U15.15 (DSP3_SSTX-)
unnamed: C47.2, U15.26 (DSP4_SSTX+)
unnamed: C50.2, U15.27 (DSP4_SSTX-)
unnamed: R26.1, U15.67 (OCP1)
unnamed: R24.1, U15.10 (OCP2)
unnamed: R25.2, U15.1 (RREF)
unnamed: C57.2, U15.60 (USP_SSTX+)
unnamed: C56.2, U15.59 (USP_SSTX-)
unnamed: C59.2, U15.55 (V33_OUT)
SD_D+: U15.5 (DSP2_DP); also elsewhere on the board
SD_D-: U15.6 (DSP2_DM); also elsewhere on the board
SD_SSRX+: C45.1; also elsewhere on the board
SD_SSRX-: C48.1; also elsewhere on the board
SD_SSTX+: U15.11 (DSP2_SSRX+); also elsewhere on the board
SD_SSTX-: U15.12 (DSP2_SSRX-); also elsewhere on the board
USB2_D+: U15.56 (USP_DP); also elsewhere on the board
USB2_D-: U15.57 (USP_DM); also elsewhere on the board
XTL0: C65.1, R27.2, U15.75 (XTLO), Y1.1
XTLI: C66.1, R27.1, U15.74 (XTLI), Y1.2
